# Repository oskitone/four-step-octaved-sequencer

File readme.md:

# Four-Step Octaved Sequencer

As featured in the blog post ["Prototype Post-Mortem: Four-Step Octaved Sequencer"](https://blog.tommy.sh/posts/prototype-post-mortem-four-step-octaved-sequencer/), these are the prototype PCB designs for a (yet to be totally finished) fun little noise toy.

The PCB and its electronics are possibly available as a [DIY electronics kit](https://www.oskitone.com/product/four-step-octaved-sequencer-kit). This repo serves as the assembly guide for the kit, as well as the EAGLE project so you can fabricate your own from scratch, should you want to!

**Demo video:** [https://vimeo.com/501110534](https://vimeo.com/501110534)  
**Order a PCB from OSH Park:** [https://oshpark.com/shared_projects/xo5nRkSm](https://oshpark.com/shared_projects/xo5nRkSm)

## Assembly guide

### Schematic

### Annotated BOM

| Part | Value   | Device                                            | Marking            | Purpose                                         |
| ---- | ------- | ------------------------------------------------- | ------------------ | ----------------------------------------------- |
| C1   | 10uF    | Polarized, electrolytic capacitor                 |                    | Tempo timer                                     |
| C2   | .1uF    | Ceramic capacitor                                 | 104                | 556 IC bypass                                   |
| C3   | 10nF    | Ceramic capacitor                                 | 103                | Pitch timer                                     |
| C4   | .1uF    | Ceramic capacitor                                 | 104                | 4017 IC bypass                                  |
| C5   | .1uF    | Ceramic capacitor                                 | 104                | 4040 IC bypass                                  |
| C6   | 220uF   | Polarized, electrolytic capacitor                 |                    | Amplifier                                       |
| D1   |         | Diode                                             |                    | Step 1 output                                   |
| D2   |         | LED                                               |                    | Step 1 indicator                                |
| D3   |         | Diode                                             |                    | Step 2 output                                   |
| D4   |         | LED                                               |                    | Step 2 indicator                                |
| D5   |         | Diode                                             |                    | Step 3 output                                   |
| D6   |         | LED                                               |                    | Step 3 indicator                                |
| D7   |         | Diode                                             |                    | Step 4 output                                   |
| D8   |         | LED                                               |                    | Step 4 indicator                                |
| IC1  | 556     | 556 Dual 555 timer                                |                    | Timers for tempo (on left) and pitch (on right) |
| IC2  | 4017    | 4017 counter/divider                              |                    | Decade counter for steps                        |
| IC3  | 4040    | CD4040 or MC14040, 12-stage binary/ripple counter |                    | Divides pitch frequency into octaves            |
| IC4  | 386     | LM386, low voltage audio power amplifier          |                    | Amplifier                                       |
| J1   | ON/OFF  | Header connection                                 |                    | For external switch (not included)              |
| J2   | - 9V +  | Header connection                                 |                    | 9v battery snap                                 |
| J3   | - SPK + | Header connection                                 |                    | To 8ohm speaker                                 |
| R1   | 680     | Resistor                                          | Blue Grey Brown    | Max tempo                                       |
| R2   | 220     | Resistor                                          | Red Red Brown      | Tempo timer                                     |
| R3   | 5.6k    | Resistor                                          | Green Blue Red     | Pitch timer                                     |
| R4   | 10k     | Resistor                                          | Brown Black Orange | Counter pulldown                                |
| R5   | 1K      | Resistor                                          | Brown Black Red    | For step 1 LED                                  |
| R6   | 1K      | Resistor                                          | Brown Black Red    | For step 2 LED                                  |
| R7   | 1K      | Resistor                                          | Brown Black Red    | For step 3 LED                                  |
| R8   | 1K      | Resistor                                          | Brown Black Red    | For step 4 LED                                  |
| R9   | 10k     | Resistor                                          | Brown Black Orange | Mixer for octave 1                              |
| R10  | 10k     | Resistor                                          | Brown Black Orange | Mixer for octave 2                              |
| R11  | 10k     | Resistor                                          | Brown Black Orange | Mixer for octave 3                              |
| R12  | 10k     | Resistor                                          | Brown Black Orange | Mixer for octave 4                              |
| SW1  |         | 4 position SPST DIP Switch                        |                    | Octave mutes                                    |
| VR1  | 50K     | Variable resistor                                 | 503                | Tempo                                           |
| VR2  | 50K     | Variable resistor                                 | 503                | Step 1 pitch                                    |
| VR3  | 50K     | Variable resistor                                 | 503                | Step 2 pitch                                    |
| VR4  | 50K     | Variable resistor                                 | 503                | Step 3 pitch                                    |
| VR5  | 50K     | Variable resistor                                 | 503                | Step 4 pitch                                    |
| VR6  | 1K      | Variable resistor                                 | 102                | Volume                                          |

Notes:

- Be sure to match polarity on electrolytic caps, diodes, and LEDs! The longer leg of the LED is positive
- The four ICs don't solder directly to the PCB. Instead, solder the included sockets, then insert ICs.
- IC3 may be marked as either CD4040 or MC14040. The two models are pin-for-pin compatible.
- The J1 (on/off) header is included for convenience if you have a switch you'd like to use. If not, short the two pads together.

### Hacking

All done? Try these ideas:

- Swap out for a bigger speaker to really hear the bass
- Increase gain on the [386](https://www.ti.com/lit/ds/symlink/lm386.pdf) with a 10uF cap between pins 1 and 8
- Try bigger pots for the step tuners
- Increase R1 for reaaalllly looongggg steeeppsssssssss
- Swap R9-12 with pots to get individual volume controls for each octave as they mix together
- The [4040](https://www.ti.com/lit/ds/symlink/cd4040b.pdf) has 12 "octave" outputs but we're only using four...

## Known issues

This PCB was last updated April 2018. In addition to the issues from the [post-mortem](https://blog.tommy.sh/posts/prototype-post-mortem-four-step-octaved-sequencer/):

- Some footprints are slightly mis-sized and require bending leads
- Volume control is linear instead of logarithmic, so range sweep isn't great
- Battery and speaker wires need relief holes to prevent breakage over time

## Version log

- **1.1.2**: Adds IC, header, and polarity labels; reorders octaves
- **1.1.1**: Adds mounting screw holes and a header for on/off switch (not included)
- **1.1**: Initial version featured in the blog post

## License

Designed by Oskitone. Please support future synth projects by purchasing from [Oskitone](https://www.oskitone.com/).

Creative Commons Attribution/Share-Alike, all text above must be included in any redistribution. See license.txt for additional details.

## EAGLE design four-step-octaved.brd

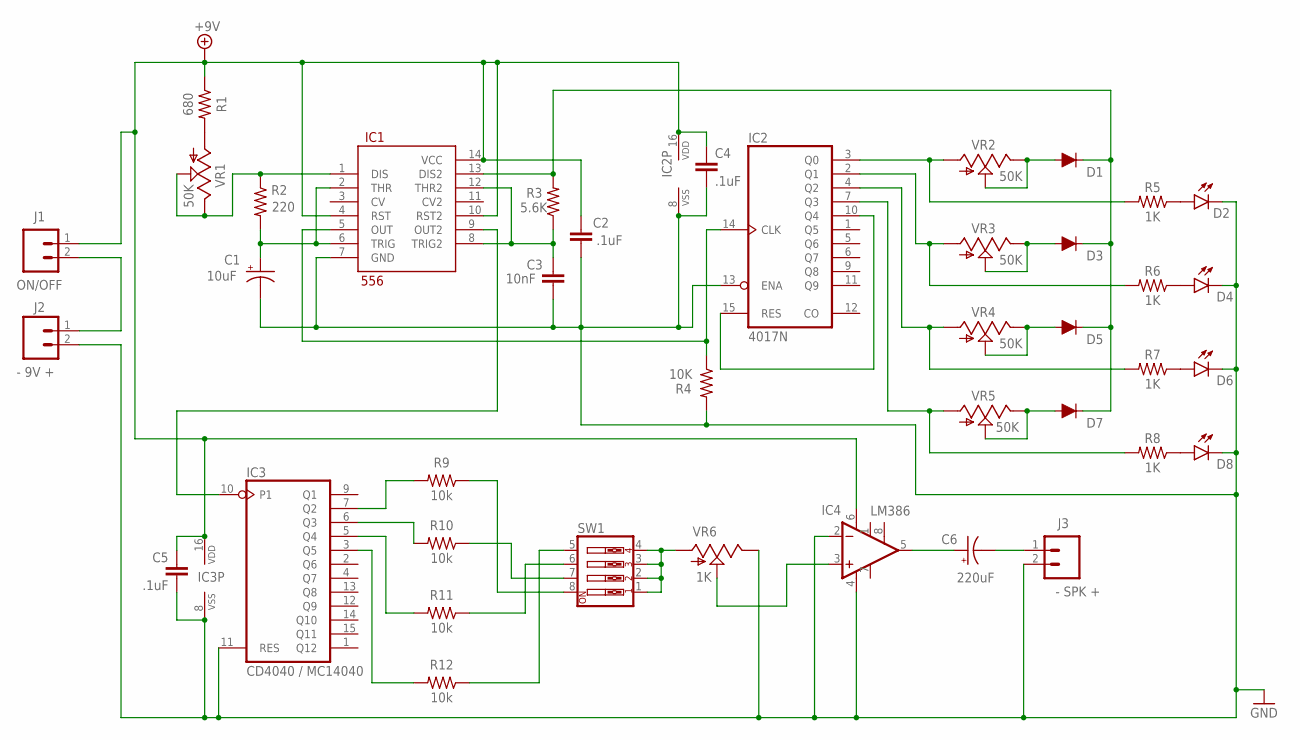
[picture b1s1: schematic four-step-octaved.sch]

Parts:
C1: 10uF; CPOL-RADIAL-2.5MM-5MM
C2, C4, C5: .1uF; CAP-PTH-SMALL-KIT
C3: 10nF; CAP-PTH-SMALL-KIT
C6: 220uF; CPOL-RADIAL-2.5MM-5MM
D1, D3, D5, D7: DIODE-PTH; DIODE-1N4001
D2, D4, D6, D8: LED3MM; LED_3MM
IC1: 556; DIP14
IC2: 4017N; DIL16
IC3: CD4040 / MC14040; DIL16
IC4: LM386; DIP08
J1: ON/OFF; 1X02
J2: - 9V +; 1X02
J3: - SPK +; 1X02
R1: 680; AXIAL-0.3
R2: 220; AXIAL-0.3
R3: 5.6K; AXIAL-0.3
R4: 10K; AXIAL-0.3
R5, R6, R7, R8: 1K; AXIAL-0.3
R9, R10, R11, R12: 10k; AXIAL-0.3
SW1: SW_DIP-4; EDG-04
VR1, VR2, VR3, VR4, VR5: 50K; TRIM_POT
VR6: 1K; TRIM_POT

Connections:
+9V: C2.1, C4.1, C5.1, IC1.4 (RST), IC1.10 (RST2), IC1.14 (VCC), IC2.16 (VDD), IC3.16 (VDD), IC4.6 (V+), J1.1, R1.P$1 (1)
GND: C1.2 (-), C2.2, C3.2, C4.2, C5.2, D2.K (C), D4.K (C), D6.K (C), D8.K (C), IC1.7 (GND), IC2.8 (VSS), IC2.13 (ENA), IC3.8 (VSS), IC3.11 (RES), IC4.2 (-IN), IC4.4 (V-), J2.2, J3.2, R4.P$2 (2), VR6.2 (E)
unnamed: R1.P$2 (2), VR1.3 (A)
unnamed: IC1.1 (DIS), R2.P$1 (1), VR1.1 (S), VR1.2 (E)
unnamed: C1.1 (+), IC1.2 (THR), IC1.6 (TRIG), R2.P$2 (2)
unnamed: IC2.10 (Q4), IC2.15 (RES)
unnamed: IC1.5 (OUT), IC2.14 (CLK), R4.P$1 (1)
unnamed: C3.1, IC1.8 (TRIG2), IC1.12 (THR2), R3.P$1 (1)
unnamed: IC2.3 (Q0), R5.P$2 (2), VR2.3 (A)
unnamed: IC2.2 (Q1), R6.P$2 (2), VR3.3 (A)
unnamed: IC2.4 (Q2), R7.P$2 (2), VR4.3 (A)
unnamed: IC2.7 (Q3), R8.P$2 (2), VR5.3 (A)
unnamed: D1.A, VR2.1 (S), VR2.2 (E)
unnamed: D8.A, R8.P$1 (1)
unnamed: D6.A, R7.P$1 (1)
unnamed: D4.A, R6.P$1 (1)
unnamed: D2.A, R5.P$1 (1)
unnamed: D3.A, VR3.1 (S), VR3.2 (E)
unnamed: D5.A, VR4.1 (S), VR4.2 (E)
unnamed: D7.A, VR5.1 (S), VR5.2 (E)
unnamed: D1.C, D3.C, D5.C, D7.C, IC1.13 (DIS2), R3.P$2 (2)
unnamed: IC3.7 (Q2), R9.P$2 (2)
unnamed: IC3.5 (Q4), R11.P$2 (2)
unnamed: IC3.6 (Q3), R10.P$2 (2)
unnamed: R12.P$1 (1), SW1.5
unnamed: IC4.3 (+IN), VR6.1 (S)
unnamed: IC3.3 (Q5), R12.P$2 (2)
unnamed: R11.P$1 (1), SW1.6
unnamed: C6.2 (-), J3.1
unnamed: C6.1 (+), IC4.5 (OUT)
unnamed: R10.P$1 (1), SW1.7
unnamed: R9.P$1 (1), SW1.8
unnamed: SW1.1, SW1.2, SW1.3, SW1.4, VR6.3 (A)
unnamed: J1.2, J2.1
unnamed: IC1.9 (OUT2), IC3.10 (P1)

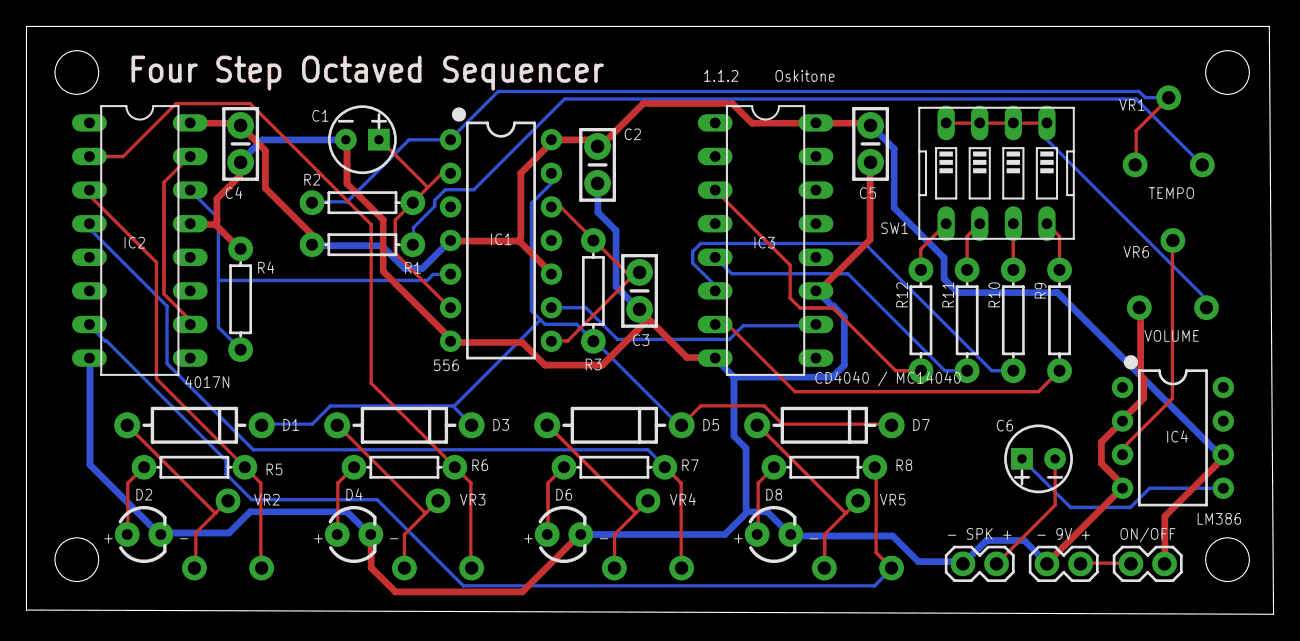
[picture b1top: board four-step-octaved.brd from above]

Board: 2 copper layers, 94.3 x 44.4 mm, 40 parts (0 on the bottom side), 35 nets.

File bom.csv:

"Part";"Value";"Device";"Package";"Description";"PROD_ID";"VALUE";
"C1";"10uF";"10UF-POLAR-RADIAL-2.5MM-25V-20%";"CPOL-RADIAL-2.5MM-5MM";"10.0µF polarized capacitors";"CAP-08440";"10uF";
"C2";".1uF";"0.1UF-KIT-EZ-50V-20%";"CAP-PTH-SMALL-KIT";"0.1µF ceramic capacitors";"CAP-08370";"0.1uF";
"C3";"10nF";"0.1UF-KIT-EZ-50V-20%";"CAP-PTH-SMALL-KIT";"0.1µF ceramic capacitors";"CAP-08370";"0.1uF";
"C4";".1uF";"0.1UF-KIT-EZ-50V-20%";"CAP-PTH-SMALL-KIT";"0.1µF ceramic capacitors";"CAP-08370";"0.1uF";
"C5";".1uF";"0.1UF-KIT-EZ-50V-20%";"CAP-PTH-SMALL-KIT";"0.1µF ceramic capacitors";"CAP-08370";"0.1uF";
"C6";"220uF";"10UF-POLAR-RADIAL-2.5MM-25V-20%";"CPOL-RADIAL-2.5MM-5MM";"10.0µF polarized capacitors";"CAP-08440";"10uF";
"D1";"";"DIODE-PTH";"DIODE-1N4001";"Diode";"DIO-09176";"1A/50V/1.1V";
"D2";"";"LED3MM";"LED_3MM";"LED (Generic)";"DIO-08794";"";
"D3";"";"DIODE-PTH";"DIODE-1N4001";"Diode";"DIO-09176";"1A/50V/1.1V";
"D4";"";"LED3MM";"LED_3MM";"LED (Generic)";"DIO-08794";"";
"D5";"";"DIODE-PTH";"DIODE-1N4001";"Diode";"DIO-09176";"1A/50V/1.1V";
"D6";"";"LED3MM";"LED_3MM";"LED (Generic)";"DIO-08794";"";
"D7";"";"DIODE-PTH";"DIODE-1N4001";"Diode";"DIO-09176";"1A/50V/1.1V";
"D8";"";"LED3MM";"LED_3MM";"LED (Generic)";"DIO-08794";"";
"IC1";"556";"556";"DIP14";"556 Dual 555 timer";"IC-11898";"556";
"IC2";"4017N";"4017N";"DIL16";"COUNTER/DIVIDER";"";"";
"IC3";"CD4040 / MC14040";"4040N";"DIL16";"12-stage binary/ripple COUNTER";"";"";
"IC4";"LM386";"LM386";"DIP08";"low voltage audio power amplifier";"IC-10899";"LM386N";
"J1";"ON/OFF";"CONN_02";"1X02";"Multi connection point. Often used as Generic Header-pin footprint for 0.1 inch spaced/style header connections";"";"";
"J2";"- 9V +";"CONN_02";"1X02";"Multi connection point. Often used as Generic Header-pin footprint for 0.1 inch spaced/style header connections";"";"";
"J3";"- SPK +";"CONN_02";"1X02";"Multi connection point. Often used as Generic Header-pin footprint for 0.1 inch spaced/style header connections";"";"";
"R1";"680";"1KOHM-HORIZ-1/4W-1%";"AXIAL-0.3";"1kΩ resistor";"RES-12182";"1k";
"R2";"220";"1KOHM-HORIZ-1/4W-1%";"AXIAL-0.3";"1kΩ resistor";"RES-12182";"1k";
"R3";"5.6K";"1KOHM-HORIZ-1/4W-1%";"AXIAL-0.3";"1kΩ resistor";"RES-12182";"1k";
"R4";"10K";"1KOHM-HORIZ-1/4W-1%";"AXIAL-0.3";"1kΩ resistor";"RES-12182";"1k";
"R5";"1K";"1KOHM-HORIZ-1/4W-1%";"AXIAL-0.3";"1kΩ resistor";"RES-12182";"1k";
"R6";"1K";"1KOHM-HORIZ-1/4W-1%";"AXIAL-0.3";"1kΩ resistor";"RES-12182";"1k";
"R7";"1K";"1KOHM-HORIZ-1/4W-1%";"AXIAL-0.3";"1kΩ resistor";"RES-12182";"1k";
"R8";"1K";"1KOHM-HORIZ-1/4W-1%";"AXIAL-0.3";"1kΩ resistor";"RES-12182";"1k";
"R9";"10k";"1KOHM-HORIZ-1/4W-1%";"AXIAL-0.3";"1kΩ resistor";"RES-12182";"1k";
"R10";"10k";"1KOHM-HORIZ-1/4W-1%";"AXIAL-0.3";"1kΩ resistor";"RES-12182";"1k";
"R11";"10k";"1KOHM-HORIZ-1/4W-1%";"AXIAL-0.3";"1kΩ resistor";"RES-12182";"1k";
"R12";"10k";"1KOHM-HORIZ-1/4W-1%";"AXIAL-0.3";"1kΩ resistor";"RES-12182";"1k";
"SW1";"";"SW_DIP-4";"EDG-04";"DIP SWITCH";"";"";
"VR1";"50K";"POTTRIM";"TRIM_POT";"";"COM-00104";"";
"VR2";"50K";"POTTRIM";"TRIM_POT";"";"COM-00104";"";
"VR3";"50K";"POTTRIM";"TRIM_POT";"";"COM-00104";"";
"VR4";"50K";"POTTRIM";"TRIM_POT";"";"COM-00104";"";
"VR5";"50K";"POTTRIM";"TRIM_POT";"";"COM-00104";"";
"VR6";"1K";"POTTRIM";"TRIM_POT";"";"COM-00104";"";

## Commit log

2017-03-25 Blank schematic init
2017-03-25 Draft 556 and 4017
2017-03-26 Tighten
2017-03-26 Add 4040 and 386
2017-03-26 Cleanup and ERC
2017-03-26 Remove lock
2017-03-26 Start board with 4017
2017-03-26 All components on board
2017-03-27 Tidier board
2017-03-27 Add board text and cleanup
2017-03-27 Shorten schematic to fit on one page
2017-03-27 Clean up board text
2017-03-27 Add net classes
2017-03-27 Routed
2017-03-28 Woof, add 1.1 board w/ switches
2017-03-28 Reorganize board
2017-03-28 Fix missing 556 pin10 on both schematics
2017-03-28 Route 1.1
2017-03-28 Fix text on wrong layer, only on 1.1
2017-03-31 Fix more text, I think
2017-04-14 Add mounting holes, increment version to 1.1.1
2017-04-14 Add LED - markers
2017-04-14 Rename RV to VR to match waltron
2017-04-14 Add switch
2017-04-14 Update 386 name
2017-04-14 Autoroute, finish
2018-01-03 Ignore and remove unnecessary files
2018-04-04 Update to 1.1.2
    - Add header label text
    - Indicate battery and speaker polarity
    - Reverse order octave switches: low to high = left to right
    - Label ICs
2021-01-13 Normalize versions
    * Remove previous version
    * Remove version filename prefix
2021-01-13 Ignore mac stuff
2021-01-13 Update mixing resistor values
    to what is actually in kits!
2021-01-13 Denote alternate 4040 chip
2021-01-13 Add BOM
2021-01-13 Fix errant RV->VR name
2021-01-14 Update eagle.pdf to newest version
    IDK if this matters at all
2021-01-15 Add readme, license, and schematic
2021-01-16 Add photos
2021-01-16 Link to video
2021-01-16 Add paper inserts design
2021-03-19 Hide unused images
2021-03-19 Fix errant purposes for mixer resistors
    and their references in the Hacking section
2026-03-12 Add link to order PCB
2026-03-12 Fix markdown table formatting

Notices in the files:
parts and their libraries:
SparkFun-Capacitors: Licensing: Creative Commons ShareAlike 4.0 International - https://creativecommons.org/licenses/by-sa/4.0
